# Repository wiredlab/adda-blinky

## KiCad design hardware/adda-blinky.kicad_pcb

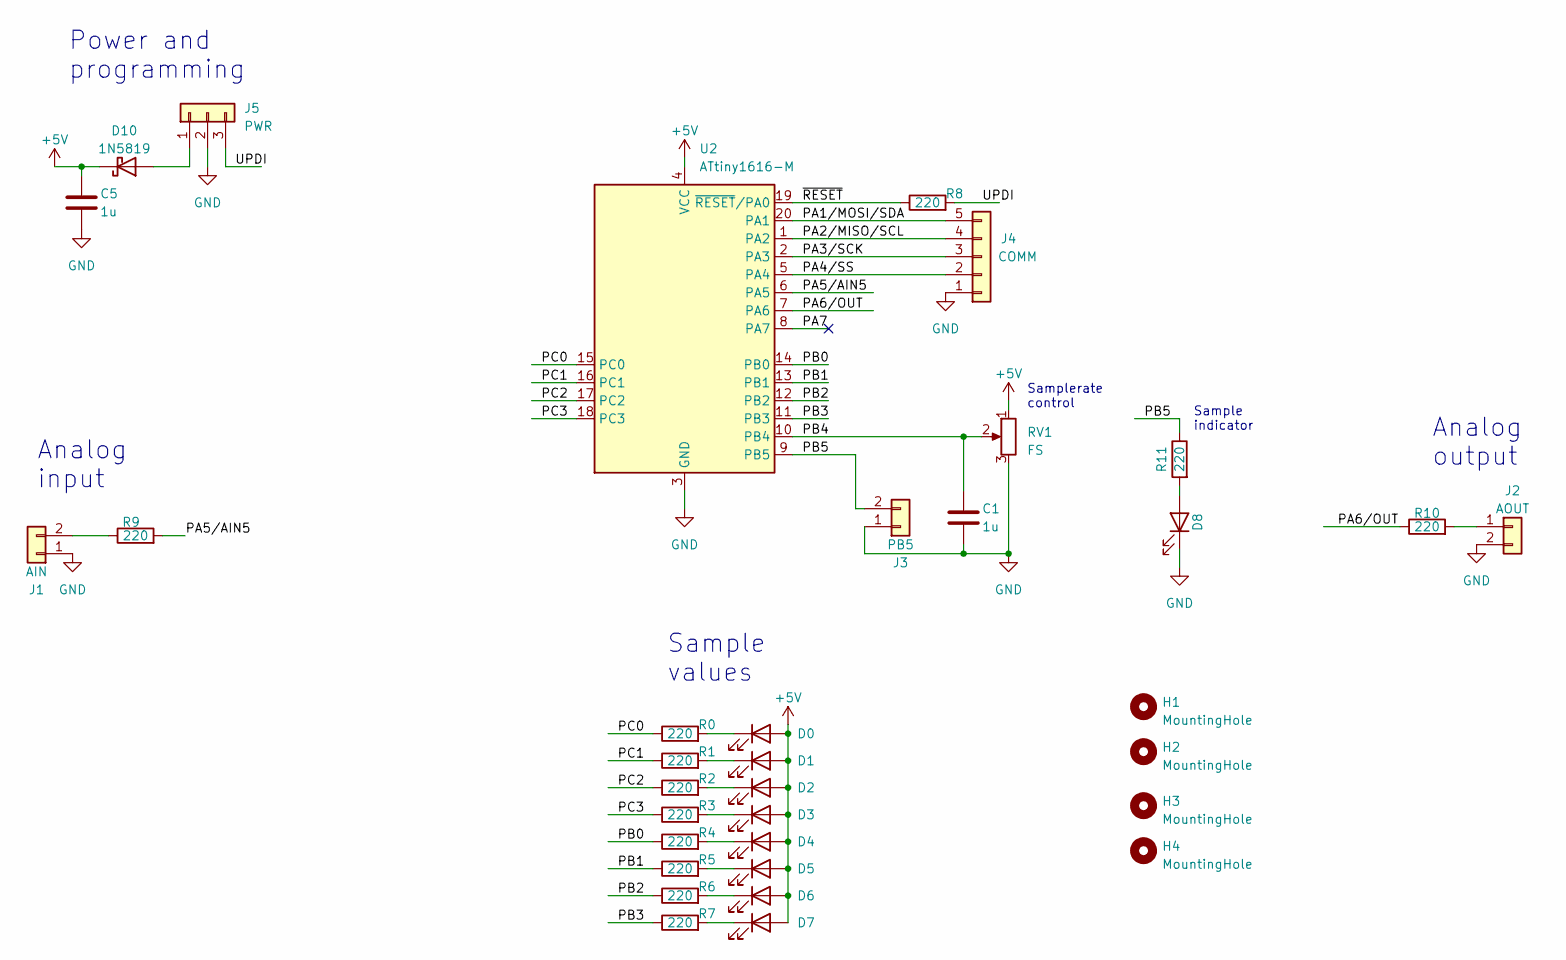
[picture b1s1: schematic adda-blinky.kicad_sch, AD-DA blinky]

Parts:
C1, C5: 1u; C_0805_2012Metric
D0, D1, D2, D3, D4, D5, D6, D7, D8: LED; D_0805_2012Metric
D10: 1N5819; D_SOD-323
H1, H2, H3, H4: MountingHole; MountingHole_3.2mm_M3_Pad
J1: AIN; Molex_KK-254_AE-6410-02A_1x02_P2.54mm_Vertical
J2: AOUT; Molex_KK-254_AE-6410-02A_1x02_P2.54mm_Vertical
J3: PB5; Molex_KK-254_AE-6410-02A_1x02_P2.54mm_Vertical
J4: COMM; Molex_KK-254_AE-6410-05A_1x05_P2.54mm_Vertical
J5: PWR; Molex_KK-254_AE-6410-03A_1x03_P2.54mm_Vertical
R0, R1, R2, R3, R4, R5, R6, R7, R8, R9, R10, R11: 220; R_0805_2012Metric
RV1: FS; PinHeader_1x03_P2.54mm_Vertical
U2: ATtiny1616-M; VQFN-20-1EP_3x3mm_P0.4mm_EP1.7x1.7mm

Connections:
+5V: C5.1, D0.2 (A), D1.2 (A), D2.2 (A), D3.2 (A), D4.2 (A), D5.2 (A), D6.2 (A), D7.2 (A), D10.1 (K), RV1.1, U2.4 (VCC)
/PA1/MOSI/SDA: J4.5, U2.20 (PA1)
/PA2/MISO/SCL: J4.4, U2.1 (PA2)
/PA3/SCK: J4.3, U2.2 (PA3)
/PA4/SS: J4.2, U2.5 (PA4)
/PA5/AIN5: R9.2, U2.6 (PA5)
/PA6/OUT: R10.1, U2.7 (PA6)
/PA7: U2.8 (PA7)
/PB0: R4.1, U2.14 (PB0)
/PB1: R5.1, U2.13 (PB1)
/PB2: R6.1, U2.12 (PB2)
/PB3: R7.1, U2.11 (PB3)
/PB4: C1.1, RV1.2, U2.10 (PB4)
/PB5: J3.2, R11.1, U2.9 (PB5)
/PC0: R0.1, U2.15 (PC0)
/PC1: R1.1, U2.16 (PC1)
/PC2: R2.1, U2.17 (PC2)
/PC3: R3.1, U2.18 (PC3)
/UPDI: J5.3, R8.2
/~RESET: R8.1, U2.19 (~RESET/PA0)
GND: C1.2, C5.2, D8.1 (K), J1.1, J2.2, J3.1, J4.1, J5.2, RV1.3, U2.3 (GND), U2.21 (GND)
unnamed: D0.1 (K), R0.2
unnamed: D1.1 (K), R1.2
unnamed: D2.1 (K), R2.2
unnamed: D3.1 (K), R3.2
unnamed: D4.1 (K), R4.2
unnamed: D5.1 (K), R5.2
unnamed: D6.1 (K), R6.2
unnamed: D7.1 (K), R7.2
unnamed: D8.2 (A), R11.2
unnamed: D10.2 (A), J5.1
unnamed: J1.2, R9.1
unnamed: J2.1, R10.2

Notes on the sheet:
Sample values
Samplerate control
Power and programming
Sample indicator
Analog output
Analog input

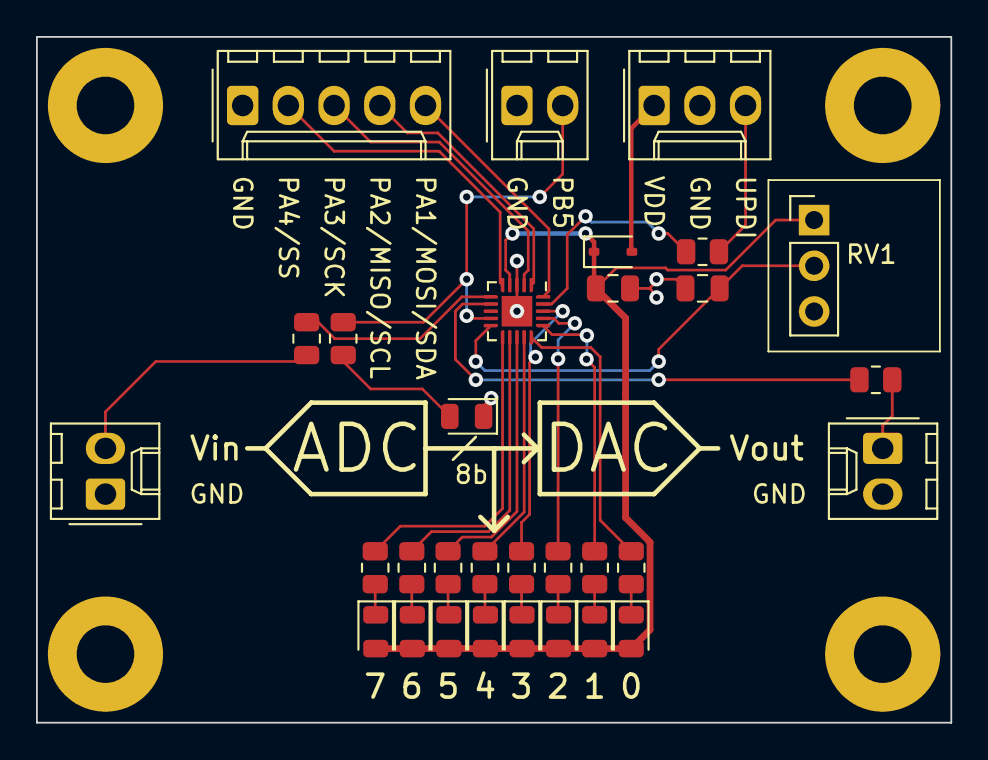
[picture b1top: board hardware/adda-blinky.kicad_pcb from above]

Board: 2 copper layers, 50.8 x 38.1 mm, 35 parts (0 on the bottom side), 32 nets.

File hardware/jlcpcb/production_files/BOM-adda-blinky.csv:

Comment,Designator,Footprint,LCSC
220,"R0,R1,R10,R11,R2,R3,R4,R5,R6,R7,R8,R9",R_0805_2012Metric,C17557
1N5819,D10,D_SOD-323,C191023
1u,"C1,C5",C_0805_2012Metric,C28323
ATtiny1616-M,U2,VQFN-20-1EP_3x3mm_P0.4mm_EP1.7x1.7mm,C507118
LED,"D0,D1,D2,D3,D4,D5,D6,D7,D8",D_0805_2012Metric,C84256
AOUT,J2,Molex_KK-254_AE-6410-02A_1x02_P2.54mm_Vertical,
AIN,J1,Molex_KK-254_AE-6410-02A_1x02_P2.54mm_Vertical,
PB5,J3,Molex_KK-254_AE-6410-02A_1x02_P2.54mm_Vertical,
COMM,J4,Molex_KK-254_AE-6410-05A_1x05_P2.54mm_Vertical,
FS,RV1,PinHeader_1x03_P2.54mm_Vertical,
PWR,J5,Molex_KK-254_AE-6410-03A_1x03_P2.54mm_Vertical,

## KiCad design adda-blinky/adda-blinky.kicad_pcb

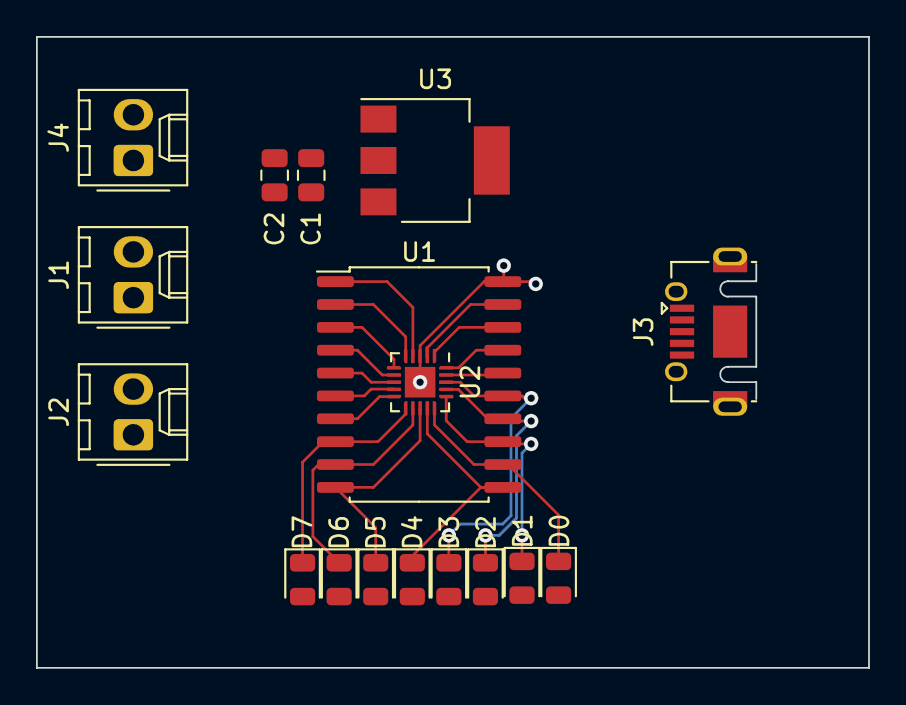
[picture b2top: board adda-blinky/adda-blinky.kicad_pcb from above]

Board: 2 copper layers, 46.2 x 35.1 mm, 17 parts (0 on the bottom side), 21 nets.

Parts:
C1, C2: 1u; C_0805_2012Metric
D0, D1, D2, D3, D4, D5, D6, D7: LED; D_0805_2012Metric
J1, J2, J4: Conn_01x02; Molex_KK-254_AE-6410-02A_1x02_P2.54mm_Vertical
J3: USB_B_Micro; USB_Micro-AB_Molex_47590-0001
U1: ATtiny1616-S; SOIC-20W_7.5x12.8mm_P1.27mm
U2: ATtiny1616-M; VQFN-20-1EP_3x3mm_P0.4mm_EP1.7x1.7mm
U3: AMS1117-3.3; SOT-223-3_TabPin2

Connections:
+3.3V: C1.1, D0.2 (A), D1.2 (A), D2.2 (A), D3.2 (A), D4.2 (A), D5.2 (A), D6.2 (A), D7.2 (A), U1.1 (VCC), U2.4 (VCC), U3.2 (VO)
+VDC: C2.1, J4.1, U3.3 (VI)
/PA1/MOSI/SDA: U1.17 (PA1), U2.20 (PA1)
/PA2/MISO/SCL: U1.18 (PA2), U2.1 (PA2)
/PA3/SCK: U1.19 (PA3), U2.2 (PA3)
/PA4/SS: U1.2 (PA4), U2.5 (PA4)
/PA5/AIN5: J1.1, U1.3 (PA5), U2.6 (PA5)
/PA6/OUT: J2.1, U1.4 (PA6), U2.7 (PA6)
/PA7: U1.5 (PA7), U2.8 (PA7)
/PB0: D4.1 (K), U1.11 (PB0), U2.14 (PB0)
/PB1: D5.1 (K), U1.10 (PB1), U2.13 (PB1)
/PB2: D6.1 (K), U1.9 (PB2), U2.12 (PB2)
/PB3: D7.1 (K), U1.8 (PB3), U2.11 (PB3)
/PB4: U1.7 (PB4), U2.10 (PB4)
/PB5: U1.6 (PB5), U2.9 (PB5)
/PC0: D0.1 (K), U1.12 (PC0), U2.15 (PC0)
/PC1: D1.1 (K), U1.13 (PC1), U2.16 (PC1)
/PC2: D2.1 (K), U1.14 (PC2), U2.17 (PC2)
/PC3: D3.1 (K), U1.15 (PC3), U2.18 (PC3)
/~RESET: U1.16 (~RESET/PA0), U2.19 (~RESET/PA0)
GND: C1.2, C2.2, J1.2, J2.2, J3.5 (GND), J3.6 (Shield), J4.2, U1.20 (GND), U2.3 (GND), U2.21 (GND), U3.1 (GND)

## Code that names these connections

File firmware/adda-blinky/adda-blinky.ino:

#define ADC_DAC_REFERENCE INTERNAL4V3
#define ANALOG_IN_PIN PIN_PA5
#define ANALOG_OUT_PIN PIN_PA6
#define SAMPLE_PIN PIN_PB5
#define POT_CHECK_INTERVAL_MS 2000
#define POT_PIN PIN_PB4

void setup() {
  // LED output pins
  // PC3..0 --> LED3..0
  PORTC.DIR = (PIN3_bm | PIN2_bm | PIN1_bm | PIN0_bm);

  // PB3..0 --> LED7..4
  PORTB.DIR = (PIN3_bm | PIN2_bm | PIN1_bm | PIN0_bm);

  // PB5 is "Sample indicator" LED
  PORTB.DIRSET = PIN5_bm;


  // Configure the ADC and DAC references
  VREF.CTRLA = (0x03 << 4) | (0x03 << 0);
  VREF.CTRLB = VREF_ADC0REFEN_bm | VREF_DAC0REFEN_bm;

  // ADC setup
  /*
  ADC0.CTRLA = ADC_RESSEL_bm | ADC_FREERUN_bm | ADC_ENABLE_bm;
  ADC0.CTRLC = ADC_SAMPCAP_bm | ADC_PRESC_DIV2_gc;
  ADC0.MUXPOS = ADC_MUXPOS_AIN5_gc;
  ADC0.COMMAND = 1;
  */
  analogReference(INTERNAL4V3);

  // DAC setup
  DAC0.CTRLA = DAC_OUTEN_bm | DAC_ENABLE_bm;


  // Configure timer to set the sample rate
  // clock divider
  TCA0.SINGLE.CTRLA = TCA_SINGLE_CLKSEL_DIV1024_gc | TCA_SINGLE_ENABLE_bm;
  TCA0.SINGLE.CTRLB = TCA_SINGLE_WGMODE_NORMAL_gc;
  TCA0.SINGLE.INTCTRL = TCA_SINGLE_OVF_bm;

  // periodic interrupt
  TCA0.SINGLE.CMP0 = 1000;
  TCA0.SINGLE.PER = 1000;

  sei();
}


void set_data_leds(int16_t data8b) {
  PORTC.OUT = (0xF0 & PORTC.OUT) | (0x0F & ~data8b);
  PORTB.OUT = (0xF0 & PORTB.OUT) | (0x0F & (~data8b >> 4));
}



void set_sample_rate(int16_t val) {
  if (val < 0x20) {
    // 1 Hz
  }
  else if (val < 0x40) {
    // 10 Hz
  }
  else if (val < 0x60) {
    // 100 Hz
  }
  else if (val < 0x80) {
    // 1 kHz
  }
  else if (val < 0xA0) {
    // 3 kHz
  }
  else if (val < 0xC0) {
    // 10 kHz
  }
  else if (val < 0xE0) {
    // 20 kHz
  }
  else {
    // max
  }
}

ISR(TCA0_OVF_vect) {
  int16_t signal_val;
  int16_t adc_raw;

  // Sample indicator
  digitalWrite(SAMPLE_PIN, 1);
  
  // sample
  
  //signal_val = 0xFF & millis()>>5;
  adc_raw = analogRead(ANALOG_IN_PIN);
  signal_val = adc_raw >> 2;

  //signal_val = analogRead(POT_PIN) >> 2;
  //signal_val = ADC0.RESL;
  
  // display
  set_data_leds(signal_val);

  // output
  //analogWrite(ANALOG_OUT_PIN, signal_val);
  DAC0.DATA = signal_val;


  // AVR 1-series needs to clear the interrupt flag
  TCA0.SINGLE.INTFLAGS = TCA_SINGLE_OVF_bm;
  ADC0.COMMAND = 1;

  // Sample indicator
  digitalWrite(SAMPLE_PIN, 0);
}



void loop() {
  unsigned long last_check = 0;
  unsigned long now;
  int16_t potval;

  now = millis();

  if ((now - last_check) > POT_CHECK_INTERVAL_MS) {
    cli();
    potval = analogRead(POT_PIN) >> 2;
    sei();
    set_sample_rate(potval);
    //set_data_leds(potval);

    //digitalWrite(PIN_PC0, ADC0.COMMAND);
    TCA0.SINGLE.PER = 20000;
    last_check = now;
  }
}

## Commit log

2023-03-04 add datasheet
2023-04-02 WIP add bus LEDs
2023-04-02 Begin block diagram
2023-04-02 Rename hardware subdir
2023-04-03 First order
2023-04-03 add fab outputs
2023-04-03 Add series resistors to I/Os
2023-04-03 Fixup MCU rotation
2023-04-03 Add LED to PB5 for status and sample indicator
2023-04-04 Swap LED orientation
2023-04-14 Add board render and update title blocks
2023-04-17 Working firmware
    Not clear yet how the timer interrupt timing is happening. It isn't yet
    matching how I predict the ISR fires.
